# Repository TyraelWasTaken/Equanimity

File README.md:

# Equanimity
## Equanimity is a 65%, gasket mounted, alice style keyboard with a knob.

There were no design goals for the project, it was simply what I wanted to see in a keyboard.

It is fully Open-Source, all files I have used to make my own I have published for everyone else to enjoy.

Firmware wise, the qmk build *should* be functional, and I am actively working on trying to publish a successful via build.

Equanimity uses cherry switches with kailh hotswap sockets, and the standard EC11 (although an EC12 should work just fine).
Also, the project uses a C series unified daughterboard with JST connectors.

The "symbol" for the equanimity is a water lily.

If you wish to build this or have any inquiries please contact me via discord and I will help you with the project.

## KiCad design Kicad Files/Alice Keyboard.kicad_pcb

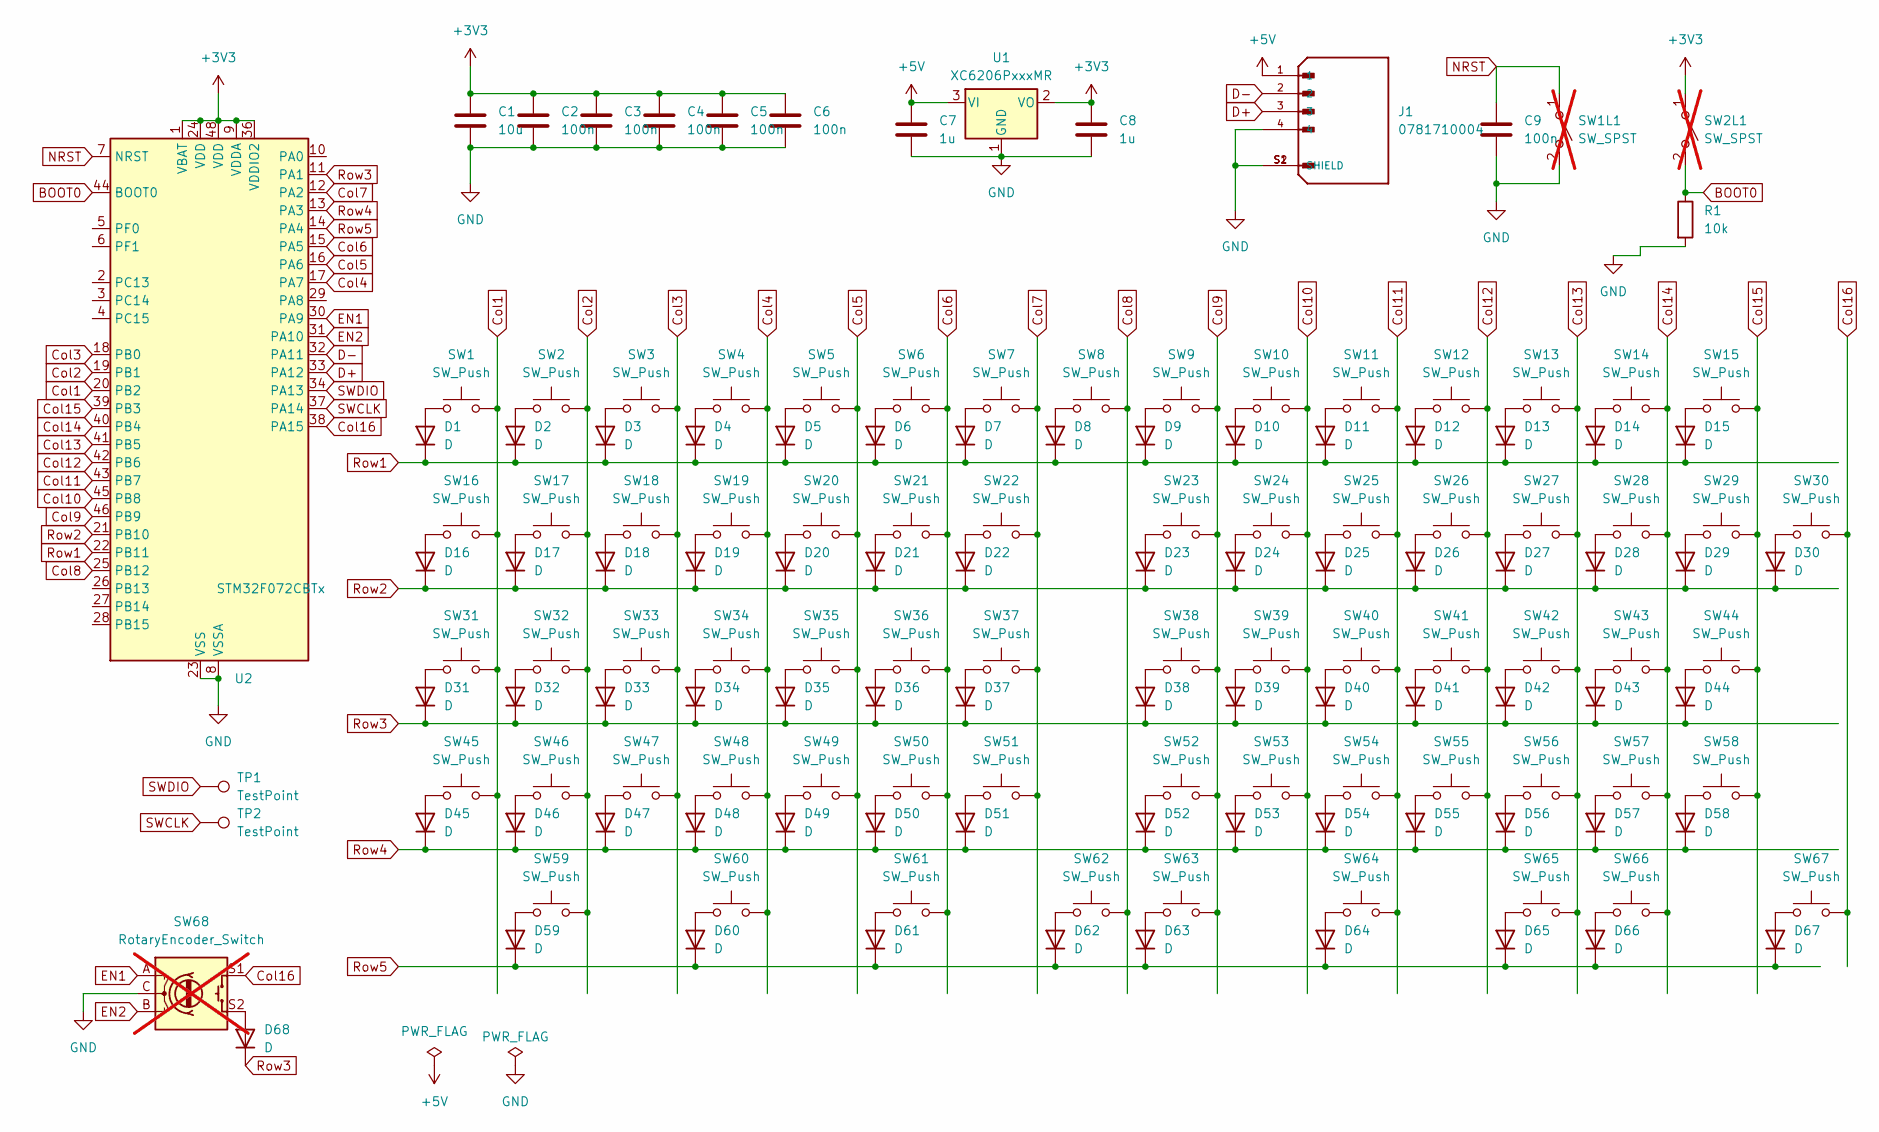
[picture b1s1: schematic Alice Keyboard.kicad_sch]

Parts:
C1: 10u; C_0805_2012Metric_Pad1.18x1.45mm_HandSolder
C2, C3, C4, C5, C6, C9: 100n; C_0603_1608Metric
C7, C8: 1u; C_0805_2012Metric_Pad1.18x1.45mm_HandSolder
D1, D2, D3, D4, D5, D6, D7, D8, D9, D10, D11, D12, D13, D14, D15, D16, D17, D18, D19, D20, D21, D22, D23, D24, D25, D26, D27, D28, D29, D30, D31, D32, D33, D34, D35, D36, D37, D38, D39, D40, D41, D42, D43, D44, D45, D46, D47, D48, D49, D50, D51, D52, D53, D54, D55, D56, D57, D58, D59, D60, D61, D62, D63, D64, D65, D66, D67, D68: D; D_SOD-123
J1: 0781710004; SM04B-SRSS-TB(LF)(SN); PARTREV G
R1: 10k; R_0805_2012Metric_Pad1.20x1.40mm_HandSolder
SW1, SW2, SW3, SW4, SW5, SW6, SW7, SW8, SW9, SW10, SW11, SW12, SW13, SW14, SW16, SW18, SW19, SW20, SW21, SW22, SW23, SW24, SW25, SW26, SW27, SW28, SW29, SW31, SW33, SW34, SW35, SW36, SW37, SW38, SW39, SW40, SW41, SW42, SW43, SW45, SW47, SW48, SW49, SW50, SW51, SW52, SW53, SW54, SW55, SW56, SW58, SW62, SW65, SW66, SW67: SW_Push; MX-Hotswap-1U
SW1L1, SW2L1: SW_SPST; SW_SPST_SKQG_WithStem; not fitted
SW15: SW_Push; MX-Hotswap-2U
SW17, SW30, SW59, SW60, SW64: SW_Push; MX-Hotswap-1.5U
SW32, SW57: SW_Push; MX-Hotswap-1.75U
SW44, SW46, SW61, SW63: SW_Push; MX-Hotswap-2.25U
SW68: RotaryEncoder_Switch; RotaryEncoder_Alps_EC11E-Switch_Vertical_H20mm; not fitted
TP1, TP2: TestPoint; Pin_D0.7mm_L6.5mm_W1.8mm_FlatFork
U1: XC6206PxxxMR; SOT-23-3
U2: STM32F072CBTx; LQFP-48_7x7mm_P0.5mm

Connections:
+3V3: C1.1, C2.1, C3.1, C4.1, C5.1, C6.1, C8.1, SW2L1.1 (A), U1.2 (VO), U2.1 (VBAT), U2.9 (VDDA), U2.24 (VDD), U2.36 (VDDIO2), U2.48 (VDD)
+5V: C7.1, J1.1, U1.3 (VI)
BOOT0: R1.1, SW2L1.2 (B), U2.44 (BOOT0)
Col1: SW1.2, SW16.2, SW31.2, SW45.2, U2.20 (PB2)
Col2: SW2.2, SW17.2, SW32.2, SW46.2, SW59.2, U2.19 (PB1)
Col3: SW3.2, SW18.2, SW33.2, SW47.2, U2.18 (PB0)
Col4: SW4.2, SW19.2, SW34.2, SW48.2, SW60.2, U2.17 (PA7)
Col5: SW5.2, SW20.2, SW35.2, SW49.2, U2.16 (PA6)
Col6: SW6.2, SW21.2, SW36.2, SW50.2, SW61.2, U2.15 (PA5)
Col7: SW7.2, SW22.2, SW37.2, SW51.2, U2.12 (PA2)
Col8: SW8.2, SW62.2, U2.25 (PB12)
Col9: SW9.2, SW23.2, SW38.2, SW52.2, SW63.2, U2.46 (PB9)
Col10: SW10.2, SW24.2, SW39.2, SW53.2, U2.45 (PB8)
Col11: SW11.2, SW25.2, SW40.2, SW54.2, SW64.2, U2.43 (PB7)
Col12: SW12.2, SW26.2, SW41.2, SW55.2, U2.42 (PB6)
Col13: SW13.2, SW27.2, SW42.2, SW56.2, SW65.2, U2.41 (PB5)
Col14: SW14.2, SW28.2, SW43.2, SW57.2, SW66.2, U2.40 (PB4)
Col15: SW15.2, SW29.2, SW44.2, SW58.2, U2.39 (PB3)
Col16: SW30.2, SW67.2, SW68.S1, U2.38 (PA15)
D+: J1.3, U2.33 (PA12)
D-: J1.2, U2.32 (PA11)
EN1: SW68.A, U2.30 (PA9)
EN2: SW68.B, U2.31 (PA10)
GND: C1.2, C2.2, C3.2, C4.2, C5.2, C6.2, C7.2, C8.2, C9.2, J1.4, J1.S1 (SHIELD), J1.S2 (SHIELD), R1.2, SW1L1.2 (B), SW68.C, U1.1 (GND), U2.8 (VSSA), U2.23 (VSS), U2.35 (VSS), U2.47 (VSS)
NRST: C9.1, SW1L1.1 (A), U2.7 (NRST)
unnamed: D1.2 (A), SW1.1
unnamed: D2.2 (A), SW2.1
unnamed: D3.2 (A), SW3.1
unnamed: D4.2 (A), SW4.1
unnamed: D5.2 (A), SW5.1
unnamed: D6.2 (A), SW6.1
unnamed: D7.2 (A), SW7.1
unnamed: D8.2 (A), SW8.1
unnamed: D9.2 (A), SW9.1
unnamed: D10.2 (A), SW10.1
unnamed: D11.2 (A), SW11.1
unnamed: D12.2 (A), SW12.1
unnamed: D13.2 (A), SW13.1
unnamed: D14.2 (A), SW14.1
unnamed: D15.2 (A), SW15.1
unnamed: D16.2 (A), SW16.1
unnamed: D17.2 (A), SW17.1
unnamed: D18.2 (A), SW18.1
unnamed: D19.2 (A), SW19.1
unnamed: D20.2 (A), SW20.1
unnamed: D21.2 (A), SW21.1
unnamed: D22.2 (A), SW22.1
unnamed: D23.2 (A), SW23.1
unnamed: D24.2 (A), SW24.1
unnamed: D25.2 (A), SW25.1
unnamed: D26.2 (A), SW26.1
unnamed: D27.2 (A), SW27.1
unnamed: D28.2 (A), SW28.1
unnamed: D29.2 (A), SW29.1
unnamed: D30.2 (A), SW30.1
unnamed: D31.2 (A), SW31.1
unnamed: D32.2 (A), SW32.1
unnamed: D33.2 (A), SW33.1
unnamed: D34.2 (A), SW34.1
unnamed: D35.2 (A), SW35.1
unnamed: D36.2 (A), SW36.1
unnamed: D37.2 (A), SW37.1
unnamed: D38.2 (A), SW38.1
unnamed: D39.2 (A), SW39.1
unnamed: D40.2 (A), SW40.1
unnamed: D41.2 (A), SW41.1
unnamed: D42.2 (A), SW42.1
unnamed: D43.2 (A), SW43.1
unnamed: D44.2 (A), SW44.1
unnamed: D45.2 (A), SW45.1
unnamed: D46.2 (A), SW46.1
unnamed: D47.2 (A), SW47.1
unnamed: D48.2 (A), SW48.1
unnamed: D49.2 (A), SW49.1
unnamed: D50.2 (A), SW50.1
unnamed: D51.2 (A), SW51.1
unnamed: D52.2 (A), SW52.1
unnamed: D53.2 (A), SW53.1
unnamed: D54.2 (A), SW54.1
unnamed: D55.2 (A), SW55.1
unnamed: D56.2 (A), SW56.1
unnamed: D57.2 (A), SW57.1
unnamed: D58.2 (A), SW58.1
unnamed: D59.2 (A), SW59.1
unnamed: D60.2 (A), SW60.1
unnamed: D61.2 (A), SW61.1
unnamed: D62.2 (A), SW62.1
unnamed: D63.2 (A), SW63.1
unnamed: D64.2 (A), SW64.1
unnamed: D65.2 (A), SW65.1
unnamed: D66.2 (A), SW66.1
unnamed: D67.2 (A), SW67.1
unnamed: D68.2 (A), SW68.S2
Row1: D1.1 (K), D2.1 (K), D3.1 (K), D4.1 (K), D5.1 (K), D6.1 (K), D7.1 (K), D8.1 (K), D9.1 (K), D10.1 (K), D11.1 (K), D12.1 (K), D13.1 (K), D14.1 (K), D15.1 (K), U2.22 (PB11)
Row2: D16.1 (K), D17.1 (K), D18.1 (K), D19.1 (K), D20.1 (K), D21.1 (K), D22.1 (K), D23.1 (K), D24.1 (K), D25.1 (K), D26.1 (K), D27.1 (K), D28.1 (K), D29.1 (K), D30.1 (K), U2.21 (PB10)
Row3: D31.1 (K), D32.1 (K), D33.1 (K), D34.1 (K), D35.1 (K), D36.1 (K), D37.1 (K), D38.1 (K), D39.1 (K), D40.1 (K), D41.1 (K), D42.1 (K), D43.1 (K), D44.1 (K), D68.1 (K), U2.11 (PA1)
Row4: D45.1 (K), D46.1 (K), D47.1 (K), D48.1 (K), D49.1 (K), D50.1 (K), D51.1 (K), D52.1 (K), D53.1 (K), D54.1 (K), D55.1 (K), D56.1 (K), D57.1 (K), D58.1 (K), U2.13 (PA3)
Row5: D59.1 (K), D60.1 (K), D61.1 (K), D62.1 (K), D63.1 (K), D64.1 (K), D65.1 (K), D66.1 (K), D67.1 (K), U2.14 (PA4)
SWCLK: TP2.1, U2.37 (PA14)
SWDIO: TP1.1, U2.34 (PA13)

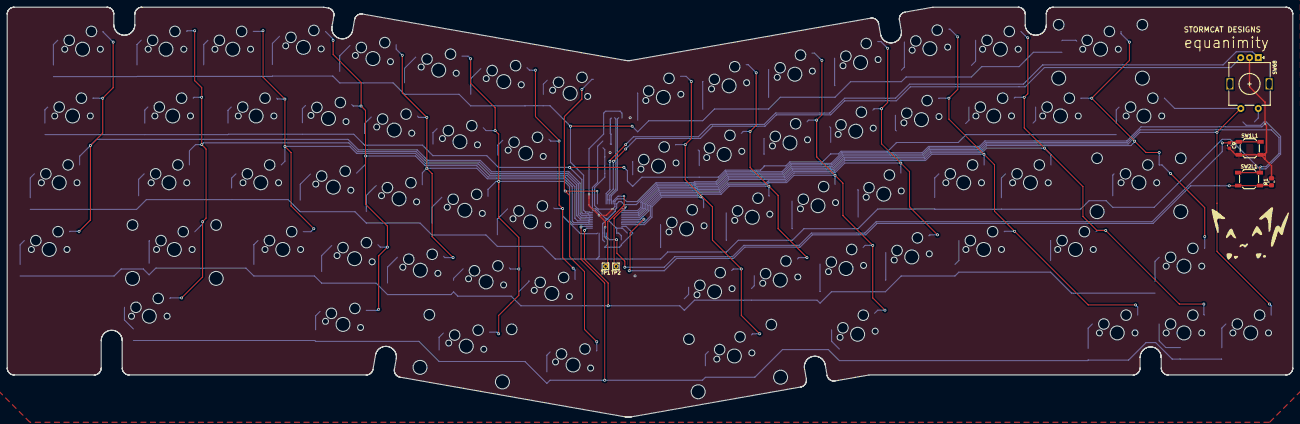
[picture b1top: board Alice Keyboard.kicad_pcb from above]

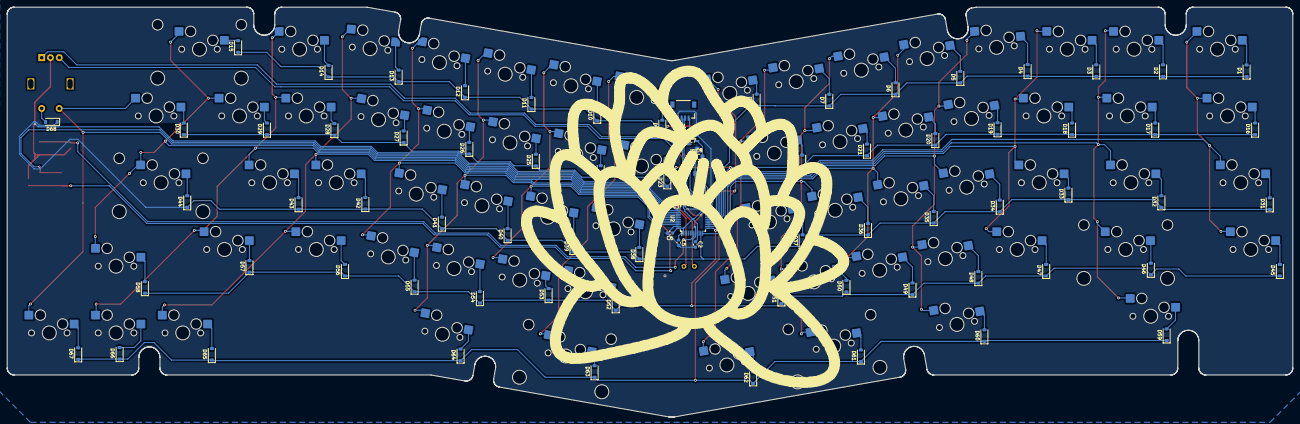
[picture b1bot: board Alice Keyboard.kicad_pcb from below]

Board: 2 copper layers, 366.9 x 117.0 mm, 153 parts (79 on the bottom side), 100 nets.

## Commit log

2024-04-24 Init
2024-04-24 Render Upload
2024-04-24 Update QMK folder
2024-06-19 Upload Encoder files
2024-06-19 Update kicad files
    The old files had an issue with the D+ and D- lines being flipped the wrong way, this has rectified this.
2024-06-19 Update QMK files
    New files add support for VIA and fixes issues with encoders and keys not functioning.
2024-06-19 Update QMK readme.md
    Add in the correct image link
